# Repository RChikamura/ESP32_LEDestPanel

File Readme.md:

# ESP32_LEDestPanel  

このプロジェクトは、**ESP32** を用いた **HUB75 LEDパネル** の行先表示システムです。  
Wi-Fi経由での制御が可能で、カスタマイズ性の高い表示システムを実現します。  

---

## **特徴**  

- **Wi-Fi制御対応**（WebSocket通信で、スマホやPCから簡単に表示切替）  
- **カスタマイズしやすいシステム設計**（ファイル差し替えだけで別路線に）  

---

## **バージョンとフォルダ**  

プロジェクトは **用途に応じた異なる方式** で開発が進行中です。  
詳細は、それぞれのフォルダ内の `README.md` を参照してください。  

| バージョン                 | 説明 | リンク |
|---------------------------|----------------------------------|---------------------------|
| **01_LittleFS_WebSocket** | LittleFS + WebSocket制御版 | [ReadMe](./01_LittleFS_WebSocket/Readme.md) |
| *02_(名称未定)* | (開発予定) |                                   |
| **aboutACR**                 | 本ソフトウェアのサンプル路線について | [ReadMe](./aboutACR/Readme.md) |
| **tools**                 | 画像変換・開発支援ツール | [ReadMe](./tools/Readme.md) |

---

## **プロジェクト情報**  

- **ライセンス**: Custom License  
- **開発者**: No Name(RChikamura)  
- **今後の開発予定**: MicroSD対応、自由スクロールなど

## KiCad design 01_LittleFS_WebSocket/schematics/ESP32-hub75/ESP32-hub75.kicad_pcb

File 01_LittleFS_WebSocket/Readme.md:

# 01_LittleFS_WebSocket

## **概要**
このバージョンは、ESP32 を用いた **HUB75 LEDパネル** の行先表示システムです。**LittleFS** を使用したファイル管理と、**WebSocket** によるリアルタイム通信をサポートしています。

---

## **特徴**
- **ESP32-WROOM-32E-N16 + オリジナル基板**（回路図は `schematics` フォルダ内）
- **Wi-Fi制御対応**（WebSocket通信で、スマホやPCからリアルタイムで表示を変更）
- **LittleFSストレージ対応**（ESP32の内部ストレージに画像や設定を保存可能）
- **動的ファイル管理**（CSVファイルを編集するだけで行き先リストをカスタマイズ可能）
- **HUB75 LEDパネル対応**（ESP32専用DMAライブラリを使用した滑らかな表示）

---

## **必要なハードウェア**
- **ESP32** (推奨ボード: [ESP32-WROOM-32E-N16](https://akizukidenshi.com/catalog/g/g115675/))  
※フラッシュサイズが16MB未満のモデル(DevKitCなど)では、エラーが出る可能性が高い。
- **専用回路基板**（schematicsフォルダにKiCadデータあり）
- **HUB75 LEDマトリクスパネル** (連結後のサイズ 128x32 推奨)
- **電源 (5V, 5A以上推奨)** (例: [5V10A スイッチング電源](https://akizukidenshi.com/catalog/g/g109086/))
- **UARTモジュール(3.3V対応)** 推奨品: [AE-TTL-232R](https://akizukidenshi.com/catalog/g/g109951/)  
※基板のフル機能を利用するには改造が必要になる([改造の概要](./docs/UART_jump.md))。

---

## **セットアップ手順**

### **1. PlatformIO のセットアップ**
1. [VS Code](https://code.visualstudio.com/) をインストール
2. [PlatformIO](https://platformio.org/install/ide?install=vscode) 拡張機能をインストール
3. `01_LittleFS_WebSocket` フォルダを **PlatformIO プロジェクトとして開く**

### **2. 必要なライブラリのインストール**
PlatformIO の **Libraries** タブを開き、以下のライブラリを検索してインストールしてください。

| ライブラリ名 | バージョン | 検索ワード | 公式リンク |
|-------------|----------|-----------|------------|
| ESP32 HUB75 LED MATRIX PANEL DMA Display | `3.0.12` | `ESP32 HUB75 LED MATRIX` | [GitHub](https://github.com/mrfaptastic/ESP32-HUB75-MatrixPanel-I2S-DMA) |
| Adafruit GFX Library | `1.11.11` | `Adafruit GFX` | [GitHub](https://github.com/adafruit/Adafruit-GFX-Library) |
| ESPAsyncWebServer-esphome | `3.3.0` | `ESPAsyncWebServer` | [GitHub](https://github.com/esphome/ESPAsyncWebServer) |

---

## **フォルダ構成**
```
01_LittleFS_WebSocket/
├── src/                 # ソースコード
│   ├── CSVReader.cpp    # CSV処理の実装
│   ├── drawBitmap.cpp   # 画像描画の実装
│   ├── main.cpp         # メインプログラム
├── data/                # LittleFS 用のデータ
│   ├── list/            # CSVファイル (行先リスト)
│   ├── img/             # 画像データ (BMP形式)
│   ├── index_CSV.html   # 操作パネル (HTML形式)
├── schematics/          # 回路図・基板データ（KiCad）
├── platformio.ini       # PlatformIO の設定
└── README.md            # このファイル
```

---

## **ビルドと書き込み**
1. **UARTモジュール**を基板と接続する。このとき、未改造モジュールを使用するならスライドスイッチをDL側に切り替える
2. **PlatformIO** の **Upload** ボタンをクリック（下側の→マーク）
3. **Upload Filesystem Image** で `data/` 内のファイルを ESP32 の **LittleFS** に書き込む
4. スライドスイッチをAuto側に切り替える。
5. **Monitor** でESP32のデバッグ情報を確認 (`monitor_speed = 115200`)。このとき、IPアドレスを控えておく

## **表示切替**
1. http://(ESP32のIPアドレス)/ にアクセスする
2. 画面を操作し、好みの表示内容にする
3. 表示更新ボタンをクリックする  
※スクロール表示の場合、スクロール生成にしばらく時間がかかるため、切り替え直後に長時間フリーズします。

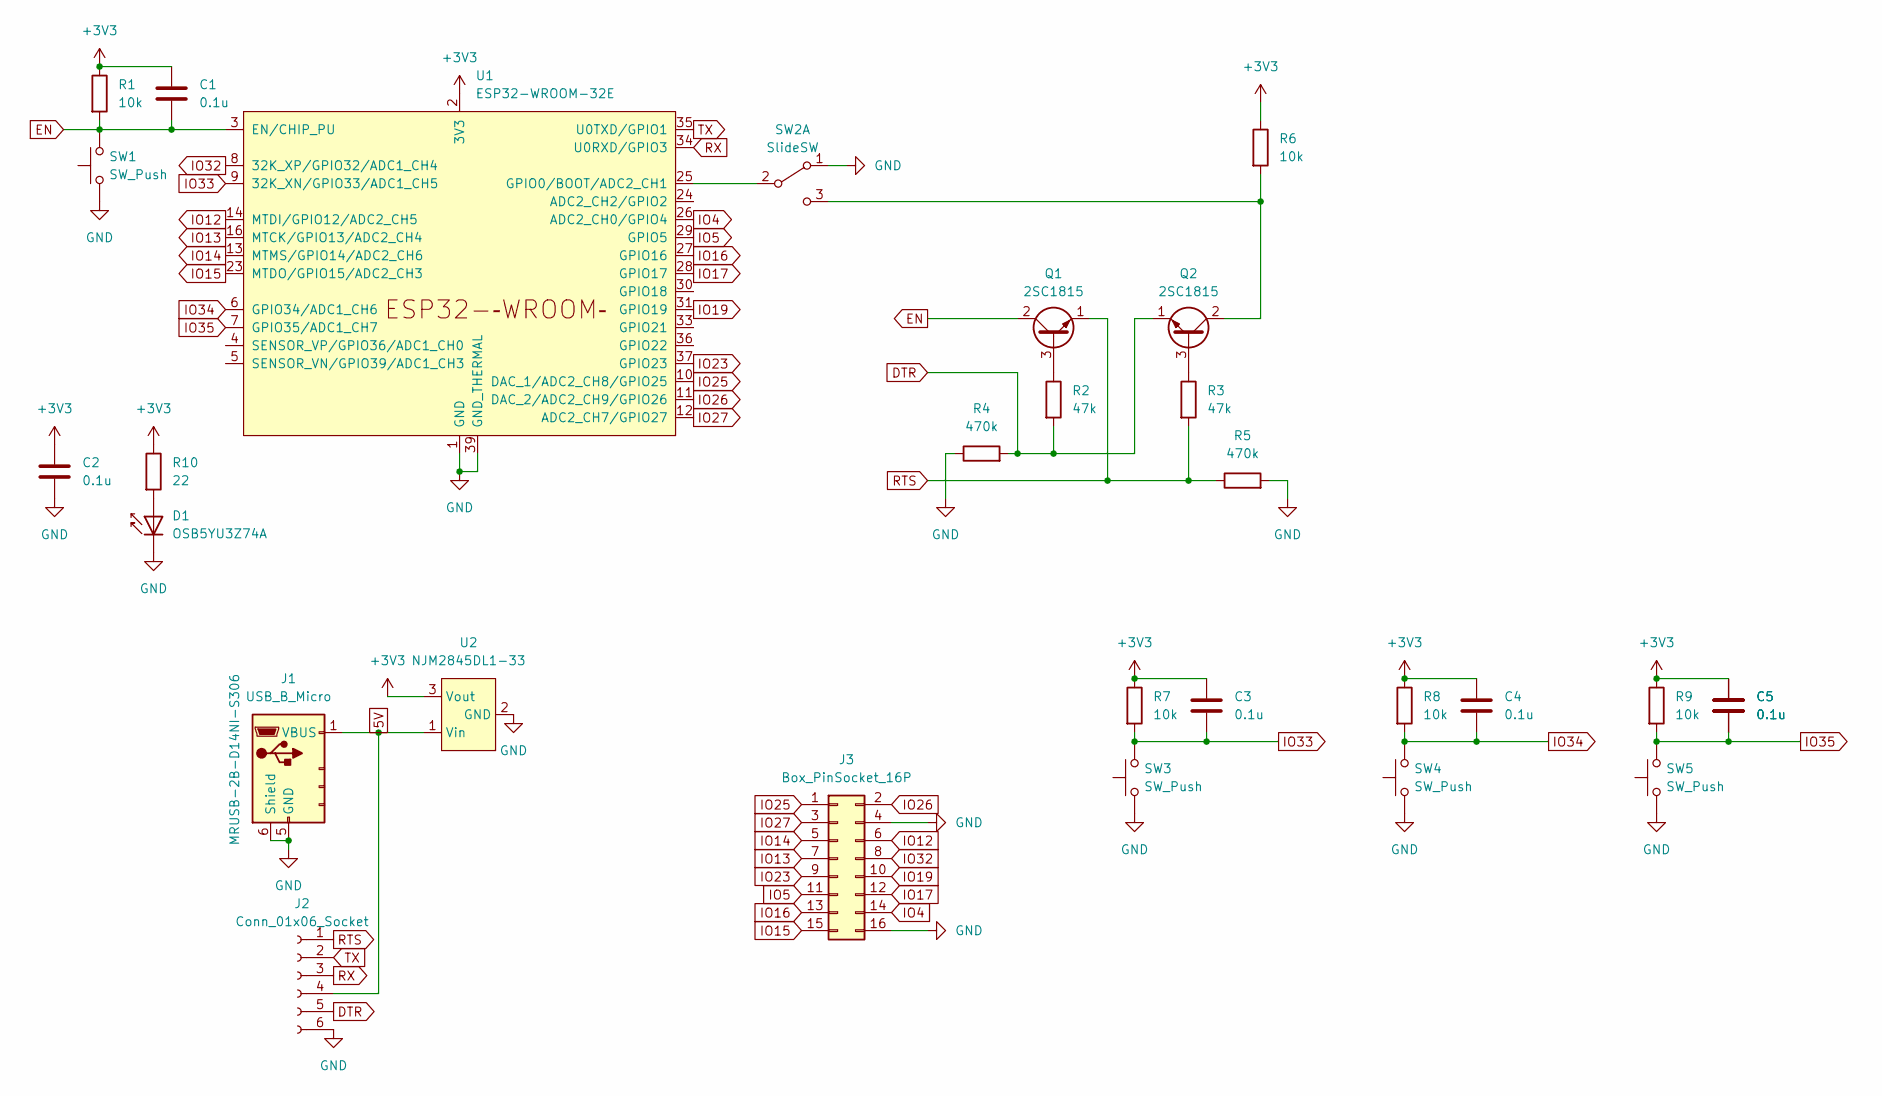
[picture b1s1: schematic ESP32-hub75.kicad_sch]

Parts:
C1, C2, C3, C4, C5: 0.1u; C_Disc_D5.0mm_W2.5mm_P5.00mm
D1: OSB5YU3Z74A; LED_D3.0mm_IRBlack
J1: USB_B_Micro; USB_Micro-B_Useconn_RUSB-2B-D14NI-S306_Horizontal
J2: Conn_01x06_Socket; PinSocket_1x06_P2.54mm_Horizontal
J3: Box_PinSocket_16P; IDC-Header_2x08_P2.54mm_Vertical
Q1, Q2: 2SC1815; TO-92_Inline
R1, R7, R8, R9: 10k; R_Axial_DIN0207_L6.3mm_D2.5mm_P7.62mm_Horizontal
R2: 47k; R_Axial_DIN0207_L6.3mm_D2.5mm_P2.54mm_Vertical
R3: 47k; R_Axial_DIN0207_L6.3mm_D2.5mm_P15.24mm_Horizontal
R4: 470k; R_Axial_DIN0207_L6.3mm_D2.5mm_P7.62mm_Horizontal
R5: 470k; R_Axial_DIN0207_L6.3mm_D2.5mm_P10.16mm_Horizontal
R6: 10k; R_Axial_DIN0207_L6.3mm_D2.5mm_P2.54mm_Vertical
R10: 22; R_Axial_DIN0207_L6.3mm_D2.5mm_P2.54mm_Vertical
SW1, SW3, SW4, SW5: SW_Push; SW_PUSH_6mm
SW2: SlideSW; SW_Slide_1P2T_P2.54
U1: ESP32-WROOM-32E
U2: NJM2845DL1-33; TO-252-3_TabPin2

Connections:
5V: J1.1 (VBUS), J2.4 (+5V), U2.1 (Vin)
+3V3: C1.1, C2.2, C3.1, C4.1, C5.1, R1.1, R6.1, R7.1, R8.1, R9.1, R10.1, U1.2 (3V3), U2.3 (Vout); also elsewhere on the board
DTR: J2.5 (DTR), Q2.1 (E), R2.2, R4.2
EN: C1.2, Q1.2 (C), R1.2, SW1.2, U1.3 (EN/CHIP_PU); also elsewhere on the board
GND: C2.1, D1.1 (K), J1.5 (GND), J1.6 (Shield), J2.6 (GND), J3.4 (GND1), J3.16 (GND3), R4.1, R5.2, SW1.1, SW2.1 (A), SW3.1, SW4.1, SW5.1, U1.1 (GND), U1.15 (GND), U1.38 (GND), U1.39 (GND_THERMAL), U2.2 (GND); also elsewhere on the board
IO4: J3.14 (LAT), U1.26 (ADC2_CH0/GPIO4); also elsewhere on the board
IO5: J3.11 (C), U1.29 (GPIO5); also elsewhere on the board
IO12: J3.6 (G2), U1.14 (MTDI/GPIO12/ADC2_CH5); also elsewhere on the board
IO13: J3.7 (B2), U1.16 (MTCK/GPIO13/ADC2_CH4); also elsewhere on the board
IO14: J3.5 (R2), U1.13 (MTMS/GPIO14/ADC2_CH6); also elsewhere on the board
IO15: J3.15 (OE), U1.23 (MTDO/GPIO15/ADC2_CH3); also elsewhere on the board
IO16: J3.13 (CLK), U1.27 (GPIO16); also elsewhere on the board
IO17: J3.12 (D), U1.28 (GPIO17); also elsewhere on the board
IO19: J3.10 (B), U1.31 (GPIO19); also elsewhere on the board
IO23: J3.9 (A), U1.37 (GPIO23); also elsewhere on the board
IO25: J3.1 (R1), U1.10 (DAC_1/ADC2_CH8/GPIO25); also elsewhere on the board
IO26: J3.2 (G1), U1.11 (DAC_2/ADC2_CH9/GPIO26); also elsewhere on the board
IO27: J3.3 (B1), U1.12 (ADC2_CH7/GPIO27); also elsewhere on the board
IO32: J3.8 (E), U1.8 (32K_XP/GPIO32/ADC1_CH4); also elsewhere on the board
IO33: C3.2, R7.2, SW3.2, U1.9 (32K_XN/GPIO33/ADC1_CH5); also elsewhere on the board
IO34: C4.2, R8.2, SW4.2, U1.6 (GPIO34/ADC1_CH6); also elsewhere on the board
IO35: C5.2, R9.2, SW5.2, U1.7 (GPIO35/ADC1_CH7); also elsewhere on the board
unnamed: D1.2 (A), R10.2
unnamed: Q1.3 (B), R2.1
unnamed: Q2.3 (B), R3.1
unnamed: Q2.2 (C), R6.2, SW2.3 (C)
unnamed 26: SW2.2 (B), U1.25 (GPIO0/BOOT/ADC2_CH1); also elsewhere on the board
RTS: J2.1 (RTS), Q1.1 (E), R3.2, R5.1
RX: J2.3 (TXD), U1.34 (U0RXD/GPIO3); also elsewhere on the board
TX: J2.2 (RXD), U1.35 (U0TXD/GPIO1); also elsewhere on the board

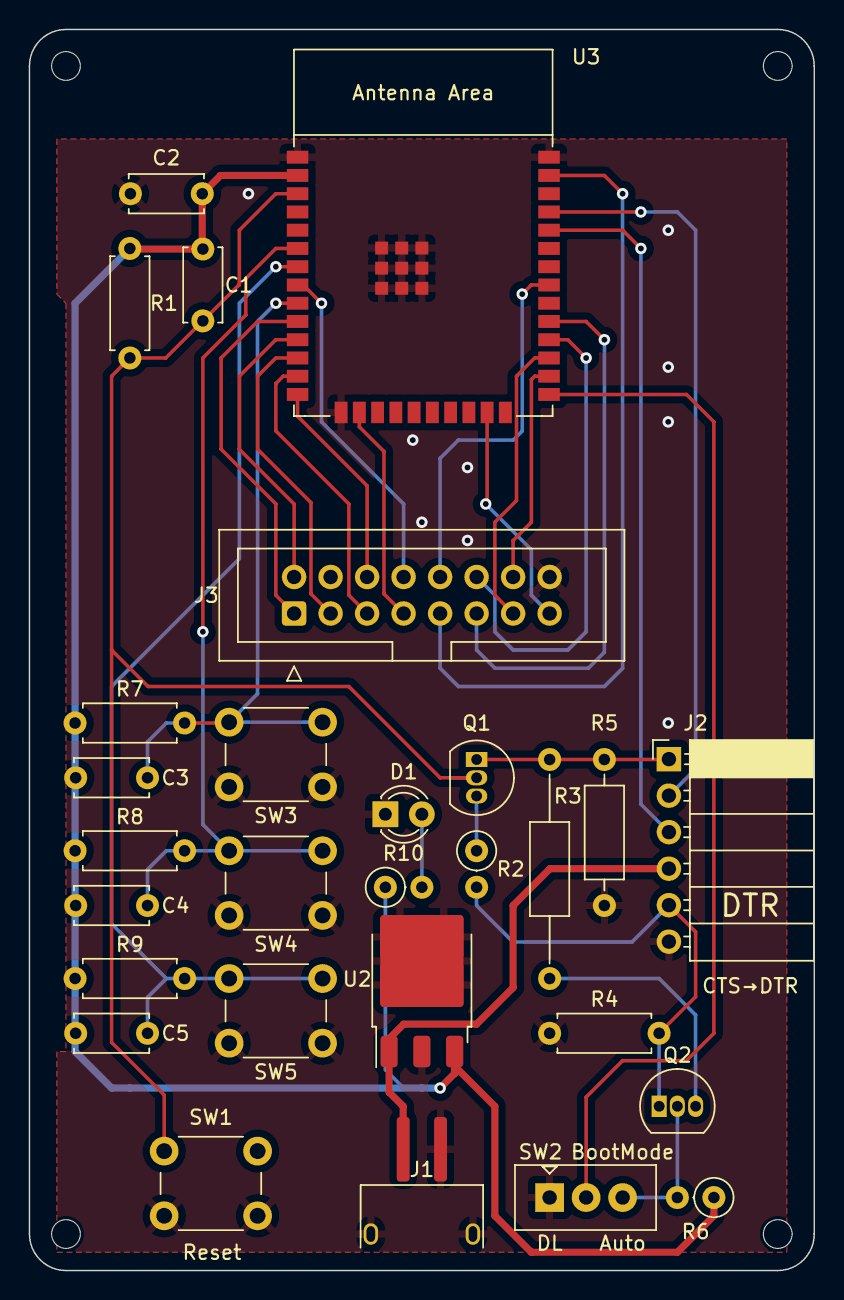
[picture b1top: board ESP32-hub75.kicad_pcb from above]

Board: 2 copper layers, 54.6 x 86.4 mm, 28 parts (0 on the bottom side), 30 nets.

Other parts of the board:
U3: ESP32-WROOM-32E

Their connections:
+3V3: U3.2 (3V3); also elsewhere on the board
EN: U3.3 (EN/CHIP_PU); also elsewhere on the board
GND: U3.1 (GND), U3.15 (GND), U3.38 (GND), U3.39 (GND_THERMAL); also elsewhere on the board
IO4: U3.26 (ADC2_CH0/GPIO4); also elsewhere on the board
IO5: U3.29 (GPIO5); also elsewhere on the board
IO12: U3.14 (MTDI/GPIO12/ADC2_CH5); also elsewhere on the board
IO13: U3.16 (MTCK/GPIO13/ADC2_CH4); also elsewhere on the board
IO14: U3.13 (MTMS/GPIO14/ADC2_CH6); also elsewhere on the board
IO15: U3.23 (MTDO/GPIO15/ADC2_CH3); also elsewhere on the board
IO16: U3.27 (GPIO16); also elsewhere on the board
IO17: U3.28 (GPIO17); also elsewhere on the board
IO19: U3.31 (GPIO19); also elsewhere on the board
IO23: U3.37 (GPIO23); also elsewhere on the board
IO25: U3.10 (DAC_1/ADC2_CH8/GPIO25); also elsewhere on the board
IO26: U3.11 (DAC_2/ADC2_CH9/GPIO26); also elsewhere on the board
IO27: U3.12 (ADC2_CH7/GPIO27); also elsewhere on the board
IO32: U3.8 (32K_XP/GPIO32/ADC1_CH4); also elsewhere on the board
IO33: U3.9 (32K_XN/GPIO33/ADC1_CH5); also elsewhere on the board
IO34: U3.6 (GPIO34/ADC1_CH6); also elsewhere on the board
IO35: U3.7 (GPIO35/ADC1_CH7); also elsewhere on the board
unnamed 26: U3.25 (GPIO0/BOOT/ADC2_CH1); also elsewhere on the board
RX: U3.34 (U0RXD/GPIO3); also elsewhere on the board
TX: U3.35 (U0TXD/GPIO1); also elsewhere on the board

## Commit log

2025-02-25 Create repository
2025-02-25 fix link for Readme
